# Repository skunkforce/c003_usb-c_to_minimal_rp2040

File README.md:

# edgy_board number c003
This design is part of the [edgy board project](https://github.com/skunkforce/edgy_boards).

# getting started
This repository uses submodules. After cloning use the command 

```$ git submodule update --init --recursive```

to pull the submodules before opening the project with kicad. 

# Tests
Tests can be found in [TESTS.md](TESTS.md)

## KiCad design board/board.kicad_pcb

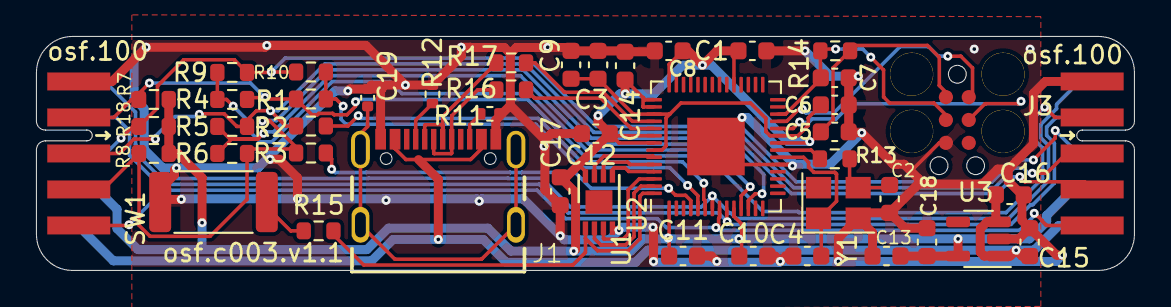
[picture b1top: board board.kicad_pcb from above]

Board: 2 copper layers, 61.0 x 13.0 mm, 47 parts (1 on the bottom side), 36 nets.

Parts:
C1, C3, C5, C6, C8, C10, C11, C12, C15: 100nF; C_0603_1608Metric
C2, C4: 12pF; C_0603_1608Metric
C7: 1nF; C_0603_1608Metric
C9, C13, C14: 2.2uF; C_0603_1608Metric
C16, C18: 1uF; C_0603_1608Metric
C17: 10uF; C_0603_1608Metric
C19: 100pF; C_0402_1005Metric
J1: USB4105-GF-A; GCT_USB4105-GF-A
J2: 100_digital_IO; on_edge_2x05_device
J3: SWD_6_Pol_Needle; SWD6pol
J4: 100_digital_IO; on_edge_2x05_host
LOGO1: Logo_Open_Hardware_Small; OSHW-Symbol_6.7x6mm_SilkScreen
R1, R2, R3, R4, R5, R6, R9, R10: 0R; R_0603_1608Metric
R7, R8: 2k; R_0603_1608Metric
R11, R12: 5.1k; R_0402_1005Metric
R13, R15: 1k; R_0603_1608Metric
R14, R18: 10k; R_0603_1608Metric
R16, R17: 27R; R_0603_1608Metric
SW1: PTS636 SK25J SMTR LFS; R_2512_6332Metric
U1: W25Q16JVUXIQ; DFN-8-1EP_3x2mm_P0.5mm_EP1.3x1.5mm
U2: RP2040; QFN-56-1EP_7x7mm_P0.4mm_EP3.2x3.2mm
U3: TLV743P; SOT-23-5
Y1: 12MhZ; Crystal_SMD_Abracon_ABM8G-4Pin_3.2x2.5mm

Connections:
+3V3: C1.1, C5.1, C8.1, C10.1, C11.1, C12.1, C13.1, C14.1, C17.1, C18.1, J2.9 (3.3V), J3.1 (VTref), J4.9 (3.3V), R7.2, R8.2, R14.1, R18.2, U1.8 (VCC), U2.1 (IOVDD), U2.10 (IOVDD), U2.22 (IOVDD), U2.33 (IOVDD), U2.42 (IOVDD), U2.43 (ADC_AVDD), U2.44 (VREG_IN), U2.48 (USB_VDD), U2.49 (IOVDD), U3.5 (VOUT)
+5V: C15.1, C16.1, J1.A4/B9 (VBUS), J1.B4/A9 (VBUS), J2.10 (5V), J4.10 (5V), U3.1 (VIN), U3.3 (~SHDN)
/GPIO0: R4.1, R9.1, U2.11 (GPIO8)
/GPIO1: R5.1, R6.1, U2.12 (GPIO9)
/GPIO2: R3.1, U2.4 (GPIO2)
/GPIO3: R1.1, R10.1, U2.5 (GPIO3)
/GPIO4: R2.1, U2.6 (GPIO4)
/GPIO5: J2.6 (IO4), J4.6 (IO4), U2.7 (GPIO5)
/GPIO6: J2.5 (IO3), J4.5 (IO3), U2.8 (GPIO6)
/GPIO7: J2.7 (IO5), J4.7 (IO5), U2.9 (GPIO7)
/rp2040/DM: R17.2, U2.46 (USB_DM)
/rp2040/DP: R16.2, U2.47 (USB_DP)
/rp2040/QPI_SS: R15.2, U1.1 (~CS), U2.56 (QSPI_SS)
/rp2040/QSPI_CLK: U1.6 (CLK), U2.52 (QSPI_SCLK)
/rp2040/RUN: C7.1, J3.3 (nRes), R14.2, U2.26 (RUN)
/rp2040/SWCLK: J3.4 (SWCLK), U2.24 (SWCLK)
/rp2040/SWD: J3.2 (SWDIO), U2.25 (SWD)
/usb-c/DM: J1.A7 (DN1), J1.B7 (DN2), R17.1
/usb-c/DP: J1.A6 (DP1), J1.B6 (DP2), R16.1
GND: C1.2, C2.2, C3.2, C4.2, C5.2, C6.2, C7.2, C8.2, C9.2, C10.2, C11.2, C12.2, C13.2, C14.2, C15.2, C16.2, C17.2, C18.2, C19.2, J1.A1/B12 (GND), J1.B1/A12 (GND), J2.1 (GND), J3.5 (GND), J4.1 (GND), R11.2, R12.2, SW1.1, U1.4 (GND), U2.19 (TESTEN), U2.57 (GND), U3.2 (GND), Y1.2, Y1.4
unnamed: C2.1, R13.1, Y1.3
unnamed: C19.1, J1.G1 (SCHIELD), J1.G2 (SCHIELD), J1.G3 (SCHIELD), J1.G4 (SCHIELD)
unnamed: J1.A5 (CC1), R12.1
unnamed: J1.B5 (CC2), R11.1
unnamed: J2.2 (IO0), J4.2 (IO0), R1.2, R4.2, R7.1
unnamed: J2.3 (IO1), J4.3 (IO1), R2.2, R5.2
unnamed: J2.4 (IO2), J4.4 (IO2), R3.2, R6.2, R8.1
unnamed: J2.8 (IO6), J4.8 (IO6), R9.2, R10.2, R18.1
unnamed: R15.1, SW1.2
unnamed: U1.5 (DI(IO0)), U2.53 (QSPI_SD0)
unnamed: U1.2 (DO(IO1)), U2.55 (QSPI_SD1)
unnamed: U1.3 (IO2), U2.54 (QSPI_SD2)
unnamed: U1.7 (IO3), U2.51 (QSPI_SD3)
unnamed: C3.1, C6.1, C9.1, U2.23 (DVDD), U2.45 (VREG_VOUT), U2.50 (DVDD)
unnamed: C4.1, U2.20 (XIN), Y1.1
unnamed: R13.2, U2.21 (XOUT)

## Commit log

2023-11-20 v1.0
2023-11-28 added boot select button
2023-11-28 fixed boot select circuit
2023-12-28 added JLC parts
2023-12-28 added straping support for different interfaces
